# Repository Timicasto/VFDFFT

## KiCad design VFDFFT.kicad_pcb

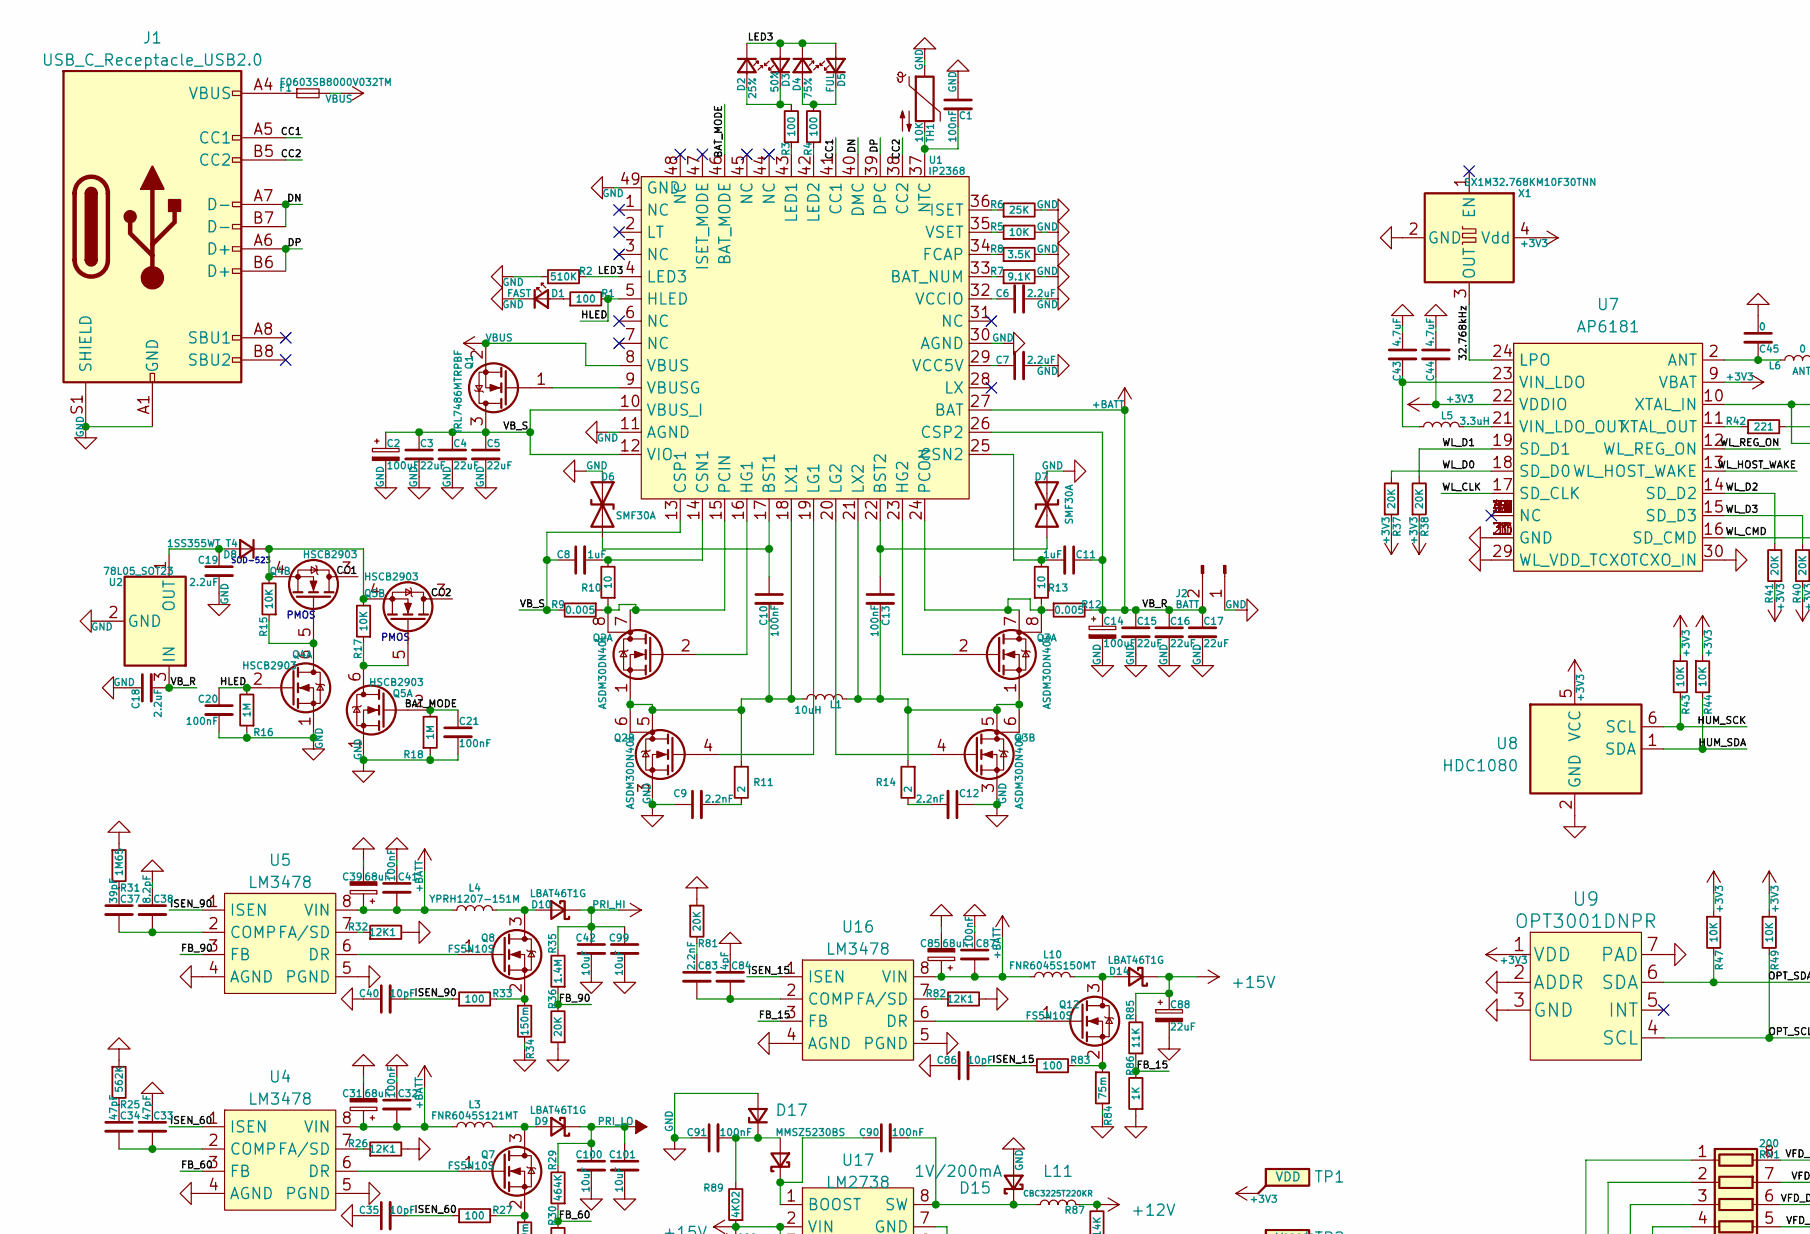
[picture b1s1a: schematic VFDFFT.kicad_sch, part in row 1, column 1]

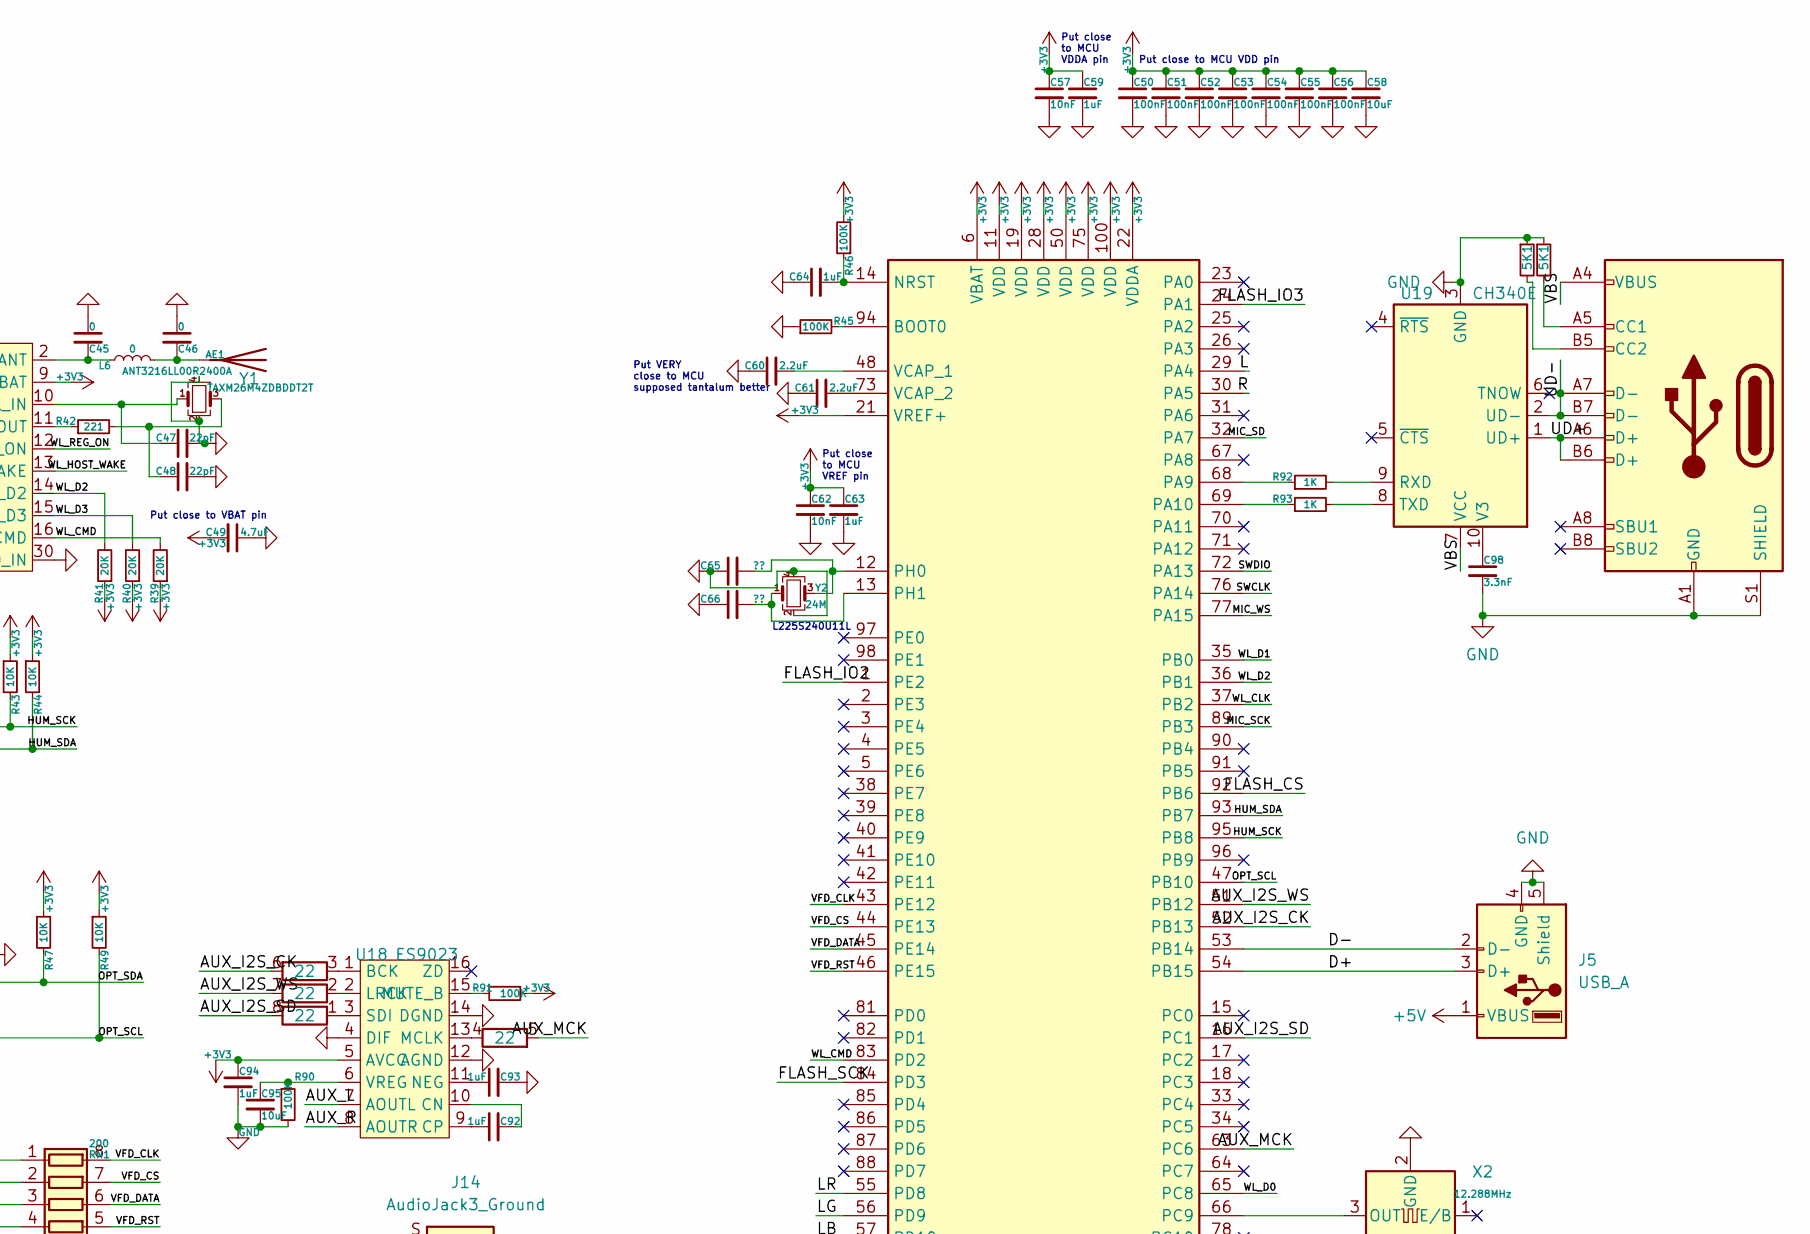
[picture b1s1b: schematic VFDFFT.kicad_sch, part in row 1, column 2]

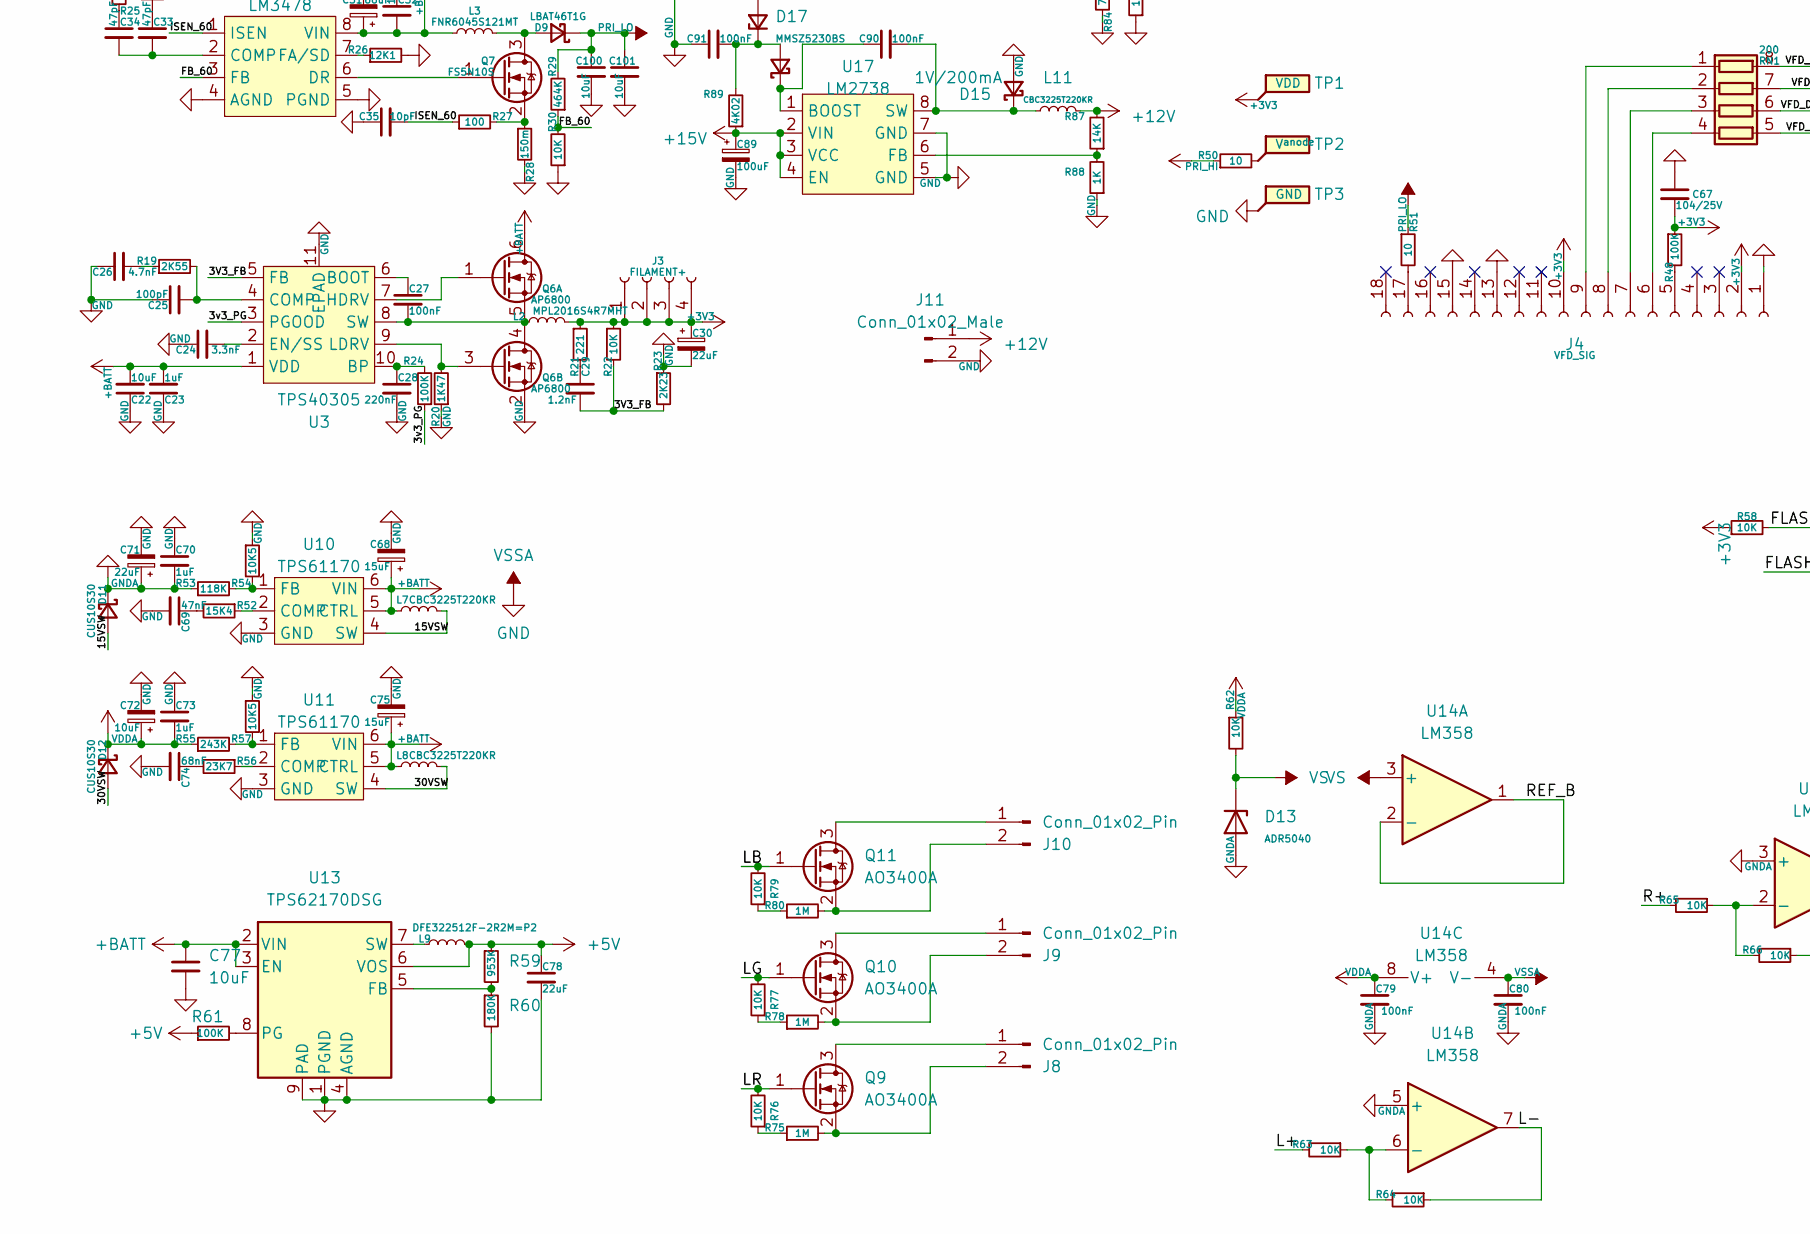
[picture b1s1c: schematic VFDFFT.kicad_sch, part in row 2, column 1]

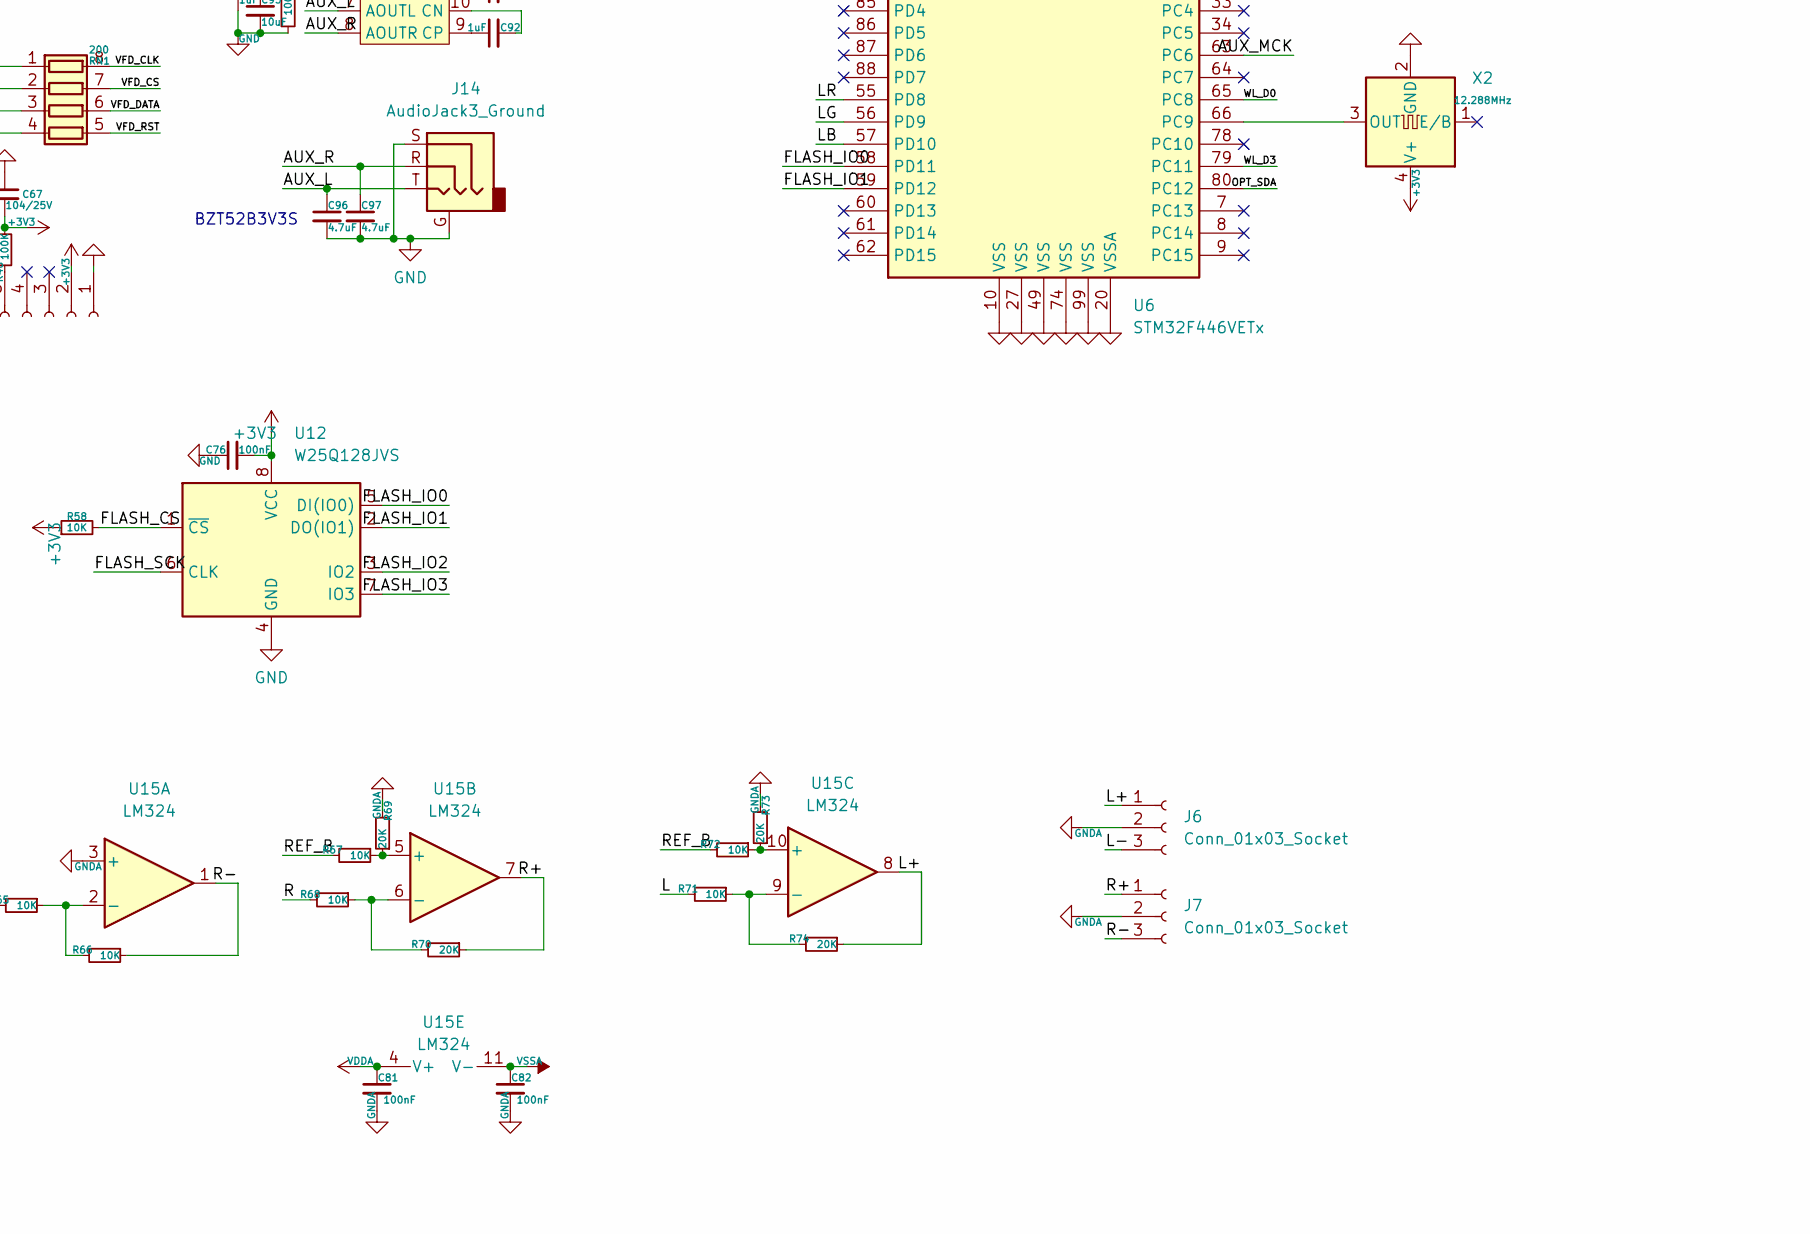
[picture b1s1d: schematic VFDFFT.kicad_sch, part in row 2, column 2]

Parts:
AE1: ANT3216LL00R2400A; R_1206_3216Metric
C1: 100nF; R_0603_1608Metric
C2, C14: 100uF; CP_EIA-7343-30_AVX-N
C3, C4, C5, C15, C16, C17, C71, C88: 22uF; C_0805_2012Metric
C6, C7, C18, C19, C60, C61: 2.2uF; C_0603_1608Metric
C8, C11, C23, C59, C63, C64, C70, C73, C92, C93, C94: 1uF; C_0603_1608Metric
C9, C12, C83: 2.2nF; C_0603_1608Metric
C10, C13, C20, C21, C27, C32, C41, C50, C51, C52, C53, C54, C55, C56, C76, C79, C80, C81, C82, C87, C90, C91: 100nF; C_0603_1608Metric
C22, C58, C72, C77, C95: 10uF; C_0603_1608Metric
C24, C98: 3.3nF; C_0603_1608Metric
C25: 100pF; C_0603_1608Metric
C26: 4.7nF; C_0603_1608Metric
C28: 220nF; C_0603_1608Metric
C29: 1.2nF; C_0603_1608Metric
C30, C78: 22uF; C_0603_1608Metric
C31, C39, C85: 68uF; CP_EIA-6032-28_Kemet-C
C33, C34: 47pF; C_0603_1608Metric
C35, C40, C86: 10pF; C_0603_1608Metric
C37: 39pF; C_0603_1608Metric
C38: 8.2pF; C_0603_1608Metric
C42, C99, C100, C101: 10uF; C_1210_3225Metric
C43, C44, C49, C96, C97: 4.7uF; C_0603_1608Metric
C45, C46: 0; C_0603_1608Metric
C47, C48: 22pF; C_0603_1608Metric
C57, C62: 10nF; C_0603_1608Metric
C65, C66: ??; C_0603_1608Metric
C67: 104/25V; C_0603_1608Metric
C68, C75: 15uF; C_0805_2012Metric
C69: 47nF; C_0603_1608Metric
C74: 68nF; C_0603_1608Metric
C84: 4pF; C_0603_1608Metric
C89: 100uF; C_0805_2012Metric
D1: FAST; D_0603_1608Metric
D2: 25%; D_0603_1608Metric
D3: 50%; D_0603_1608Metric
D4: 75%; D_0603_1608Metric
D5: FUL; D_0603_1608Metric
D6, D7: SMF30A; D_SOD-123F
D8: 1SS355WT T4; D_SOD-523
D9: LBAT46T1G; D_1206_3216Metric
D10: LBAT46T1G; SOD-323HE
D11, D12: CUS10S30; D_SOD-323
D13: ADR5040; SOT-23
D14: LBAT46T1G; D_SOD-123
D15, D16: 1V/200mA; D_SOD-523
D17: MMSZ5230BS; D_SOD-323
F1: F0603SB8000V032TM; Fuse_0603_1608Metric
J1, J15: USB_C_Receptacle_USB2.0; TYPE-C-31-M-31
J2: BATT; SolderWire-1sqmm_1x02_P5.4mm_D1.4mm_OD2.7mm
J3: FILAMENT+; PinHeader_1x04_P2.00mm_Vertical
J4: VFD_SIG; PinHeader_1x18_P2.00mm_Vertical
J5: USB_A; FCI_87520-0010BLF
J6, J7: Conn_01x03_Socket; PinSocket_1x03_P2.00mm_Vertical_SMD_Pin1Right
J8, J9, J10: Conn_01x02_Pin; PinSocket_1x02_P2.00mm_Vertical_SMD_Pin1Right
J11: Conn_01x02_Male; PinSocket_1x02_P2.00mm_Vertical_SMD_Pin1Right
J14: AudioJack3_Ground; TRRS-PJ-320A
L1: 10uH; L_11x10mm_H3.80
L2: MPL2016S4R7MHT; L_0806_2016Metric
L3: FNR6045S121MT; L_6.3x6.3_H3
L4: YPRH1207-151M; L_6.3x6.3_H3
L5: 3.3uH; L_1008_2520Metric
L6: 0; L_0603_1608Metric
L7, L8, L11: CBC3225T220KR; L_1210_3225Metric
L9: DFE322512F-2R2M=P2; L_1008_2520Metric
L10: FNR6045S150MT; L_6.3x6.3_H3
Q1: IRL7486MTRPBF; PDFN_3x3_GSD
Q2, Q3: ASDM30DN40E; PDFN3333-8
Q4, Q5: HSCB2903; DFN-6L-2EP-2x2
Q6: AP6800; SOT-23-6
Q7, Q8, Q12: FS5N10S; SOT-23
Q9, Q10, Q11: AO3400A; SOT-23
R1, R3, R4, R27, R33, R83: 100; R_0603_1608Metric
R2: 510K; R_0603_1608Metric
R5, R15, R17, R22, R30, R43, R44, R47, R49, R58, R62, R63, R64, R65, R66, R67, R68, R71, R72, R76, R77, R79: 10K; R_0603_1608Metric
R6: 25K; R_0603_1608Metric
R7: 9.1K; R_0603_1608Metric
R8: 3.5K; R_0603_1608Metric
R9: 0.005; R_1206_3216Metric
R10: 10; R_0805_2012Metric
R11, R14: 2; R_0603_1608Metric
R12: 0.005; R_0805_2012Metric
R13, R50, R51: 10; R_0603_1608Metric
R16, R18, R75, R78, R80: 1M; R_0603_1608Metric
R19: 2K55; R_0603_1608Metric
R20: 1K47; R_0603_1608Metric
R21, R42: 221; R_0603_1608Metric
R23: 2K23; R_0603_1608Metric
R24, R45, R46, R48, R61, R90, R91: 100K; R_0603_1608Metric
R25: 562K; R_0603_1608Metric
R26, R32, R82: 12K1; R_0603_1608Metric
R28, R34: 150m; R_0603_1608Metric
R29: 464K; R_0603_1608Metric
R31: 1M65; R_0603_1608Metric
R35: 1.4M; R_0603_1608Metric
R36, R37, R38, R39, R40, R41, R69, R70, R73, R74, R81: 20K; R_0603_1608Metric
R52: 15K4; R_0603_1608Metric
R53: 118K; R_0603_1608Metric
R54, R57: 10K5; R_0603_1608Metric
R55: 243K; R_0603_1608Metric
R56: 23K7; R_0603_1608Metric
R59: 953K; R_0603_1608Metric
R60: 180K; R_0603_1608Metric
R84: 75m; R_0603_1608Metric
R85: 11K; R_0603_1608Metric
R86, R88, R92, R93: 1K; R_0603_1608Metric
R87: 14K; R_0603_1608Metric
R89: 4K02; R_0603_1608Metric
R94, R95: 5K1; R_0603_1608Metric
RN1: 200; R_Array_Concave_4x0603
RN2: 22; R_Array_Concave_4x0603
TH1: 10K; R_0603_1608Metric
TP1: VDD; TestPoint_Pad_1.0x1.0mm
TP2: V^{anode}; TestPoint_Pad_1.0x1.0mm
TP3: GND; TestPoint_Pad_1.0x1.0mm
U1: IP2368; QFN-48-1EP_7x7mm_P0.5mm_EP5.3x5.3mm
U2: 78L05_SOT23; SOT-89-3
U3: TPS40305; DFN-10-1EP_3x3mm_P0.5mm_EP1.65x2.38mm
U4, U5, U16: LM3478; VSSOP-8_3.0x3.0mm_P0.65mm
U6: STM32F446VETx; LQFP-100_14x14mm_P0.5mm
U7: AP6181; QFN-44_12x12_Pitch0.9mm
U8: HDC1080; Texas_PWSON-N6
U9: OPT3001DNPR
U10, U11: TPS61170; WSON-6-1EP_2x2mm_P0.65mm_EP1x1.6mm
U12: W25Q128JVS; SOIC-8_5.23x5.23mm_P1.27mm
U13: TPS62170DSG; WSON-8-1EP_2x2mm_P0.5mm_EP0.9x1.6mm_ThermalVias
U14: LM358; VSSOP-8_3.0x3.0mm_P0.65mm
U15: LM324; TSSOP-14_4.4x5mm_P0.65mm
U17: LM2738; VSSOP-8_3.0x3.0mm_P0.65mm
U18: ES9023; SO-16_3.9x9.9mm_P1.27mm
U19: CH340E; MSOP-10_3x3mm_P0.5mm
X1: SX1M32.768KM10F30TNN; Crystal_SMD_2016-4Pin_2.0x1.6mm
X2: 12.288MHz; Crystal_SMD_2016-4Pin_2.0x1.6mm
Y1: TAXM26M4ZDBDDT2T; Crystal_SMD_2016-4Pin_2.0x1.6mm
Y2: 24M; Crystal_SMD_2016-4Pin_2.0x1.6mm

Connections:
+3V3: C30.1, C44.2, C49.2, C50.1, C51.1, C52.1, C53.1, C54.1, C55.1, C56.1, C57.1, C58.1, C59.1, C62.1, C63.1, C67.2, C76.2, C94.1, J3.1, J3.2, J3.3, J3.4, J4.2, J4.10, L2.2, R21.1, R22.1, R37.1, R38.1, R39.1, R40.1, R41.1, R43.1, R44.1, R46.2, R47.1, R48.1, R49.1, R58.1, R91.1, TP1.1, U6.6 (VBAT), U6.11 (VDD), U6.19 (VDD), U6.21 (VREF+), U6.22 (VDDA), U6.28 (VDD), U6.50 (VDD), U6.75 (VDD), U6.100 (VDD), U7.9 (VBAT), U7.22 (VDDIO), U8.5 (VCC), U9.1 (VDD), U12.8 (VCC), U18.5 (AVCC), X1.4 (Vdd), X2.4 (V+)
+5V: C78.1, J5.1 (VBUS), L9.2, R59.1, R61.1, U13.6 (VOS)
+12V: J11.1, L11.2, R87.2
+15V: C88.1, C89.1, D14.1 (K), R85.2, R89.1, U17.2 (VIN), U17.3 (VCC), U17.4 (EN)
+BATT: C11.1, C14.1, C15.1, C16.1, C17.1, C18.2, C22.2, C23.2, C31.1, C32.2, C39.1, C41.2, C68.1, C75.1, C77.1, C85.1, C87.2, J2.2, L3.1, L4.1, L7.1, L8.1, L10.1, Q6.6 (D), R12.2, U1.26 (CSP2), U1.27 (BAT), U2.3 (IN), U3.1 (VDD), U4.8 (VIN), U5.8 (VIN), U10.5 (CTRL), U10.6 (VIN), U11.5 (CTRL), U11.6 (VIN), U13.2 (VIN), U13.3 (EN), U16.8 (VIN)
/3V3_FB: C29.2, R22.2, R23.2, U3.5 (FB)
/3v3_PG: R24.1, U3.3 (PGOOD)
/15VSW: D11.2 (A), L7.2, U10.4 (SW)
/30VSW: D12.2 (A), L8.2, U11.4 (SW)
/32.768kHz: U7.24 (LPO), X1.3 (OUT)
/AUX_I2S_CK: RN2.6 (R3.2), U6.52 (PB13)
/AUX_I2S_SD: RN2.8 (R1.2), U6.16 (PC1)
/AUX_I2S_WS: RN2.7 (R2.2), U6.51 (PB12)
/AUX_L: C96.1, J14.T, U18.7 (AOUTL)
/AUX_MCK: RN2.5 (R4.2), U6.63 (PC6)
/AUX_R: C97.1, J14.R, U18.8 (AOUTR)
/BAT_MODE: C21.1, Q5.2 (G), R18.2, U1.46 (BAT_MODE)
/CC1: J1.A5 (CC1), Q4.3 (D), U1.41 (CC1)
/CC2: J1.B5 (CC2), Q5.3 (D), U1.38 (CC2)
/D+: J5.3 (D+), U6.54 (PB15)
/D-: J5.2 (D-), U6.53 (PB14)
/DN: J1.A7 (D-), J1.B7 (D-), U1.40 (DMC)
/DP: J1.A6 (D+), J1.B6 (D+), U1.39 (DPC)
/FB_15: R85.1, R86.2, U16.3 (FB)
/FB_60: R29.1, R30.2, U4.3 (FB)
/FB_90: R35.1, R36.2, U5.3 (FB)
/FLASH_CS: R58.2, U6.92 (PB6), U12.1 (~CS)
/FLASH_IO0: U6.58 (PD11), U12.5 (DI(IO0))
/FLASH_IO1: U6.59 (PD12), U12.2 (DO(IO1))
/FLASH_IO2: U6.1 (PE2), U12.3 (IO2)
/FLASH_IO3: U6.24 (PA1), U12.7 (IO3)
/FLASH_SCK: U6.84 (PD3), U12.6 (CLK)
/HLED: C20.1, Q4.2 (G), R1.2, R16.2, U1.5 (HLED)
/HUM_SCK: R43.2, U6.95 (PB8), U8.6 (SCL)
/HUM_SDA: R44.2, U6.93 (PB7), U8.1 (SDA)
/ISEN_15: C86.2, R83.1, U16.1 (ISEN)
/ISEN_60: C35.2, R27.1, U4.1 (ISEN)
/ISEN_90: C40.2, R33.1, U5.1 (ISEN)
/L: R71.2, U6.29 (PA4)
/L+: J6.1, R63.2, R74.1, U15.8
/L-: J6.3, R64.1, U14.7
/LB: Q11.1 (G), R79.2, U6.57 (PD10)
/LED3: D2.1 (K), D3.2 (A), D4.1 (K), D5.2 (A), R2.2, U1.4 (LED3)
/LG: Q10.1 (G), R77.2, U6.56 (PD9)
/LR: Q9.1 (G), R76.2, U6.55 (PD8)
/MIC_SCK: U6.89 (PB3)
/MIC_SD: U6.32 (PA7)
/MIC_WS: U6.77 (PA15)
/OPT_SCL: R49.2, U6.47 (PB10), U9.4 (SCL)
/OPT_SDA: R47.2, U6.80 (PC12), U9.6 (SDA)
/R: R68.2, U6.30 (PA5)
/R+: J7.1, R65.2, R70.1, U15.7
/R-: J7.3, R66.1, U15.1
/REF_B: R67.2, R72.2, U14.1, U14.2 (-)
/SWCLK: U6.76 (PA14)
/SWDIO: U6.72 (PA13)
/UD+: J15.A6 (D+), J15.B6 (D+), U19.1 (UD+)
/UD-: J15.A7 (D-), J15.B7 (D-), U19.2 (UD-)
/VBS: J15.A4 (VBUS), J15.A9 (VBUS), J15.B4 (VBUS), J15.B9 (VBUS), U19.7 (VCC)
/VB_S: C2.1, C3.1, C4.1, C5.1, C8.1, Q1.3 (D), R9.2, U1.10 (VBUS_I), U1.12 (VIO), U1.13 (CSP1)
/VFD_CLK: RN1.8 (R1.2), U6.43 (PE12)
/VFD_CS: RN1.7 (R2.2), U6.44 (PE13)
/VFD_DATA: RN1.6 (R3.2), U6.45 (PE14)
/VFD_RST: RN1.5 (R4.2), U6.46 (PE15)
/WL_CLK: U6.37 (PB2), U7.17 (SD_CLK)
/WL_CMD: R39.2, U6.83 (PD2), U7.16 (SD_CMD)
/WL_D0: R37.2, U6.65 (PC8), U7.18 (SD_D0)
/WL_D1: R38.2, U6.35 (PB0), U7.19 (SD_D1)
/WL_D2: R41.2, U6.36 (PB1), U7.14 (SD_D2)
/WL_D3: R40.2, U6.79 (PC11), U7.15 (SD_D3)
/WL_HOST_WAKE: U7.13 (WL_HOST_WAKE)
/WL_REG_ON: U7.12 (WL_REG_ON)
GND: C1.1, C2.2, C3.2, C4.2, C5.2, C6.2, C7.2, C9.1, C12.1, C14.2, C15.2, C16.2, C17.2, C18.1, C19.2, C20.2, C21.2, C22.1, C23.1, C24.1, C25.1, C26.1, C28.2, C30.2, C31.2, C32.1, C33.1, C35.1, C38.1, C39.2, C40.1, C41.1, C42.2, C43.1, C44.1, C45.1, C46.1, C47.2, C48.2, C49.1, C50.2, C51.2, C52.2, C53.2, C54.2, C55.2, C56.2, C57.2, C58.2, C59.2, C60.1, C61.1, C62.2, C63.2, C64.1, C65.1, C66.1, C67.1, C68.2, C69.2, C70.1, C71.2, C72.2, C73.1, C74.2, C75.2, C76.1, C77.2, C78.2, C80.1, C82.1, C84.1, C85.2, C86.1, C87.1, C88.2, C89.2, C91.1, C93.2, C94.2, C95.2, C96.2, C97.2, C98.2, C99.2, C100.2, C101.2, D1.1 (K), D6.1 (A1), D7.1 (A1), D15.2 (A), D17.2 (A), J1.A1 (GND), J1.A12 (GND), J1.B1 (GND), J1.B12 (GND), J1.S1 (SHIELD), J2.1, J4.1, J4.13, J4.15, J5.4 (GND), J5.5 (Shield), J11.2, J14.G, J14.S, J15.A1 (GND), J15.A12 (GND), J15.B1 (GND), J15.B12 (GND), J15.S1 (SHIELD), Q2.3 (S), Q3.3 (S), Q4.1 (S), Q5.1 (S), Q6.2 (S), R2.1, R5.2, R6.2, R7.2, R8.2, R16.1, R18.1, R20.1, R23.1, R25.1, R26.2, R28.2, R30.1, R31.1, R32.2, R34.2, R36.1, R45.1, R54.1, R57.1, R60.2, R81.1, R82.2, R84.2, R86.1, R88.1, R90.2, R94.1, R95.1, TH1.1, TP3.1, U1.11 (AGND), U1.30 (AGND), U1.49 (GND), U2.2 (GND), U3.11 (EPAD), U4.4 (AGND), U4.5 (PGND), U5.4 (AGND), U5.5 (PGND), U6.10 (VSS), U6.20 (VSSA), U6.27 (VSS), U6.49 (VSS), U6.74 (VSS), U6.99 (VSS), U7.1 (GND), U7.3 (GND), U7.20 (GND), U7.29 (WL_VDD_TCXO), U7.30 (TCXO_IN), U7.31 (GND), U7.33 (GND), U8.2 (GND), U9.2 (ADDR), U9.3 (GND), U9.7 (PAD), U10.3 (GND), U11.3 (GND), U12.4 (GND), U13.1 (PGND), U13.4 (AGND), U13.9 (PAD), U14.4 (V-), U15.11 (V-), U16.4 (AGND), U16.5 (PGND), U17.5 (GND), U17.7 (GND), U17.9 (GND), U18.4 (DIF), U18.12 (AGND), U18.14 (DGND), U19.3 (GND), X1.2 (GND), X2.2 (GND), Y1.2, Y1.4, Y2.2, Y2.4
GNDA: C70.2, C71.1, C79.2, C80.2, C81.2, C82.2, D11.1 (K), D13.2 (A), J6.2, J7.2, R53.1, R69.2, R73.2, U14.5 (+), U15.3 (+)
unnamed: AE1.1 (A), C46.2, L6.2
unnamed: C9.2, R11.2
unnamed: C12.2, R14.2
unnamed: C26.2, R19.1
unnamed: C29.1, R21.2
unnamed: C34.1, R25.2
unnamed: C37.1, R31.2
unnamed: C48.1, R42.2, Y1.3
unnamed: C69.1, R52.2
unnamed: C74.1, R56.2
unnamed: C83.1, R81.2
unnamed: D1.2 (A), R1.1
unnamed: D2.2 (A), D3.1 (K), R3.2
unnamed: D4.2 (A), D5.1 (K), R4.2
unnamed: C10.1, D6.2 (A2), U1.17 (BST1)
unnamed: C13.1, D7.2 (A2), U1.22 (BST2)
unnamed: C19.1, D8.2 (A), U2.1 (OUT)
unnamed: D8.1 (K), Q4.4 (S), Q5.4 (S), R15.2, R17.2
unnamed: D9.2 (A), L3.2, Q7.3 (D)
unnamed: D10.2 (A), L4.2, Q8.3 (D)
unnamed: D14.2 (A), L10.2, Q12.3 (D)
unnamed: C90.2, D15.1 (K), L11.1, U17.8 (SW)
unnamed: C91.2, D16.2 (A), D17.1 (K), R89.2
unnamed: C90.1, D16.1 (K), U17.1 (BOOST)
unnamed: F1.1, J1.A4 (VBUS), J1.A9 (VBUS), J1.B4 (VBUS), J1.B9 (VBUS)
unnamed: J4.5, R48.2
unnamed: J4.6, RN1.4 (R4.1)
unnamed: J4.7, RN1.3 (R3.1)
unnamed: J4.8, RN1.2 (R2.1)
unnamed: J4.9, RN1.1 (R1.1)
unnamed: J4.17, R51.2
unnamed: J8.1, Q9.3 (D)
unnamed: J8.2, Q9.2 (S), R75.2
unnamed: J9.1, Q10.3 (D)
unnamed: J9.2, Q10.2 (S), R78.2
unnamed: J10.1, Q11.3 (D)
unnamed: J10.2, Q11.2 (S), R80.2
unnamed: J15.A5 (CC1), R95.2
unnamed: J15.B5 (CC2), R94.2
unnamed: Q1.1 (G), U1.9 (VBUSG)
unnamed: Q2.2 (G), U1.16 (HG1)
unnamed: C10.2, L1.1, Q2.1 (S), Q2.5 (D), Q2.6 (D), R11.1, U1.18 (LX1)
unnamed: Q2.4 (G), U1.19 (LG1)
unnamed: Q3.2 (G), U1.23 (HG2)
unnamed: C13.2, L1.2, Q3.1 (S), Q3.5 (D), Q3.6 (D), R14.1, U1.21 (LX2)
unnamed: Q3.4 (G), U1.20 (LG2)
unnamed: Q4.5 (G), Q4.6 (D), R15.1
unnamed: Q5.5 (G), Q5.6 (D), R17.1
unnamed: Q6.1 (G), U3.7 (HDRV)
unnamed: C27.2, L2.1, Q6.4 (D), Q6.5 (S), U3.8 (SW)
unnamed: Q6.3 (G), R20.2, U3.9 (LDRV)
unnamed: Q7.1 (G), U4.6 (DR)
unnamed: Q7.2 (S), R27.2, R28.1
unnamed: Q8.1 (G), U5.6 (DR)
unnamed: Q8.2 (S), R33.2, R34.1
unnamed: Q12.1 (G), U16.6 (DR)
unnamed: Q12.2 (S), R83.2, R84.1
unnamed: R50.2, TP2.1
unnamed: R75.1, R76.1
unnamed: R77.1, R78.1
unnamed: R79.1, R80.1
unnamed: RN2.1 (R1.1), U18.3 (SDI)
unnamed: RN2.2 (R2.1), U18.2 (LRCK)
unnamed: RN2.3 (R3.1), U18.1 (BCK)
unnamed: RN2.4 (R4.1), U18.13 (MCLK)
unnamed: R7.1, U1.33 (BAT_NUM)
unnamed: C8.2, R10.2, U1.14 (CSN1)
unnamed: C11.2, R13.2, U1.25 (CSN2)
unnamed: R8.1, U1.34 (FCAP)
unnamed: R6.1, U1.36 (ISET)
unnamed: R3.1, U1.43 (LED1)
unnamed: R4.1, U1.42 (LED2)
unnamed: C1.2, TH1.2, U1.37 (NTC)
unnamed: Q2.7 (D), Q2.8 (D), R9.1, R10.1, U1.15 (PCIN)
unnamed: Q3.7 (D), Q3.8 (D), R12.1, R13.1, U1.24 (PCON)
unnamed: C7.1, U1.29 (VCC5V)
unnamed: C6.1, U1.32 (VCCIO)
unnamed: R5.1, U1.35 (VSET)
unnamed: C27.1, U3.6 (BOOT)
unnamed: C28.1, R24.2, U3.10 (BP)
unnamed: C25.2, R19.2, U3.4 (COMP)
unnamed: C24.2, U3.2 (EN/SS)
unnamed: C33.2, C34.2, U4.2 (COMP)
unnamed: R26.1, U4.7 (FA/SD)
unnamed: C37.2, C38.2, U5.2 (COMP)
unnamed: R32.1, U5.7 (FA/SD)
unnamed: R45.2, U6.94 (BOOT0)
unnamed: C64.2, R46.1, U6.14 (NRST)
unnamed: R92.1, U6.68 (PA9)
unnamed: R93.1, U6.69 (PA10)
unnamed: U6.66 (PC9), X2.3 (OUT)
unnamed: C65.2, U6.12 (PH0), Y2.3
unnamed: C66.2, U6.13 (PH1), Y2.1
unnamed: C60.2, U6.48 (VCAP_1)
unnamed: C61.2, U6.73 (VCAP_2)
unnamed: C45.2, L6.1, U7.2 (ANT)
unnamed: C43.2, L5.1, U7.23 (VIN_LDO)
unnamed: L5.2, U7.21 (VIN_LDO_OUT)
unnamed: C47.1, U7.10 (XTAL_IN), Y1.1
unnamed: R42.1, U7.11 (XTAL_OUT)
unnamed: R52.1, U10.2 (COMP)
unnamed: R53.2, R54.2, U10.1 (FB)
unnamed: R56.1, U11.2 (COMP)
unnamed: R55.2, R57.2, U11.1 (FB)
unnamed: R59.2, R60.1, U13.5 (FB)
unnamed: R61.2, U13.8 (PG)
unnamed: L9.1, U13.7 (SW)
unnamed: R63.1, R64.2, U14.6 (-)
unnamed: R65.1, R66.2, U15.2 (-)
unnamed: R67.1, R69.1, U15.5 (+)
unnamed: R68.1, R70.2, U15.6 (-)
unnamed: R72.1, R73.1, U15.10 (+)
unnamed: R71.1, R74.2, U15.9 (-)
unnamed: C83.2, C84.2, U16.2 (COMP)
unnamed: R82.1, U16.7 (FA/SD)
unnamed: R87.1, R88.2, U17.6 (FB)
unnamed: C92.2, U18.10 (CN)
unnamed: C92.1, U18.9 (CP)
unnamed: R91.2, U18.15 (MUTE_B)
unnamed: C93.1, U18.11 (NEG)
unnamed: C95.1, R90.1, U18.6 (VREG)
unnamed: R92.2, U19.9 (RXD)
unnamed: R93.2, U19.8 (TXD)
unnamed: C98.1, U19.10 (V3)
PRI_HI: C42.1, C99.1, D10.1 (K), R35.2, R50.1
PRI_LO: C100.1, C101.1, D9.1 (K), R29.2, R51.1
VBUS: F1.2, Q1.2 (S), U1.8 (VBUS)
VDDA: C72.1, C73.2, C79.1, C81.1, D12.1 (K), R55.1, R62.1, U14.8 (V+), U15.4 (V+)
VS: D13.1 (K), R62.2, U14.3 (+)

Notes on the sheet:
Put close to MCU VDDA pin
Put VERY close to MCU supposed tantalum better
Put close to MCU VREF pin
SOD-523
Put close to MCU VDD pin
BZT52B3V3S
PMOS
L225S240U11L
Put close to VBAT pin

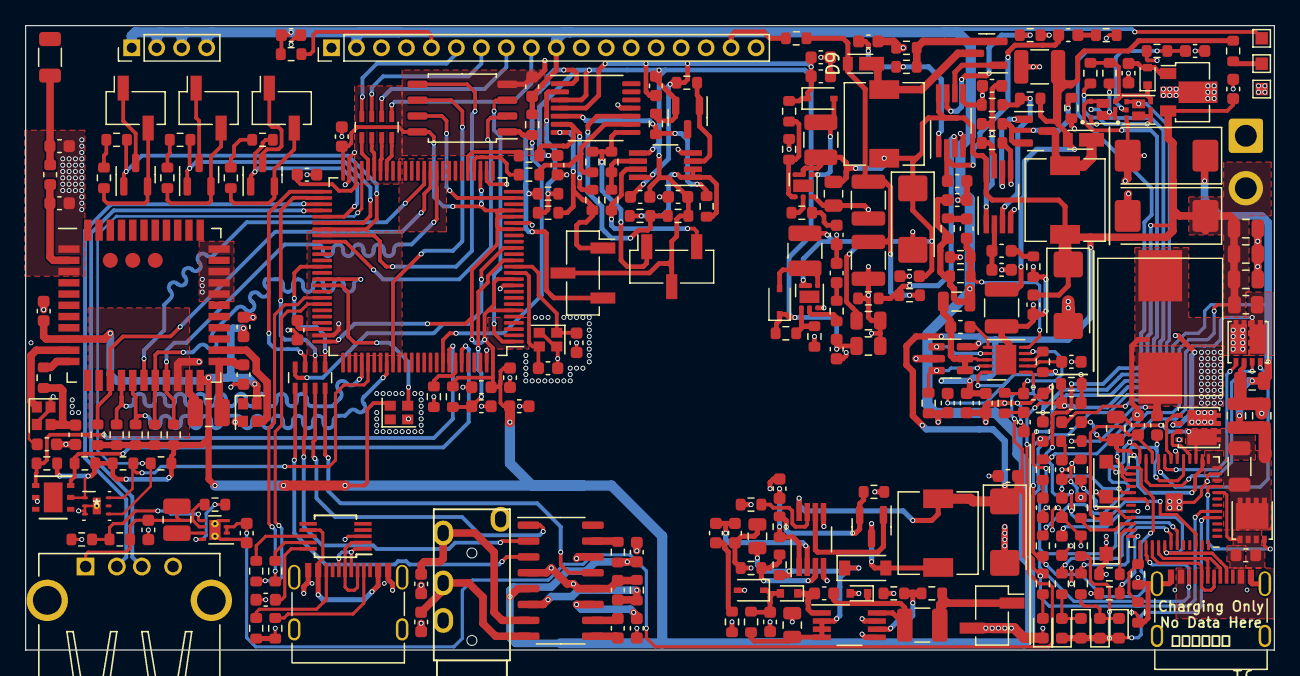
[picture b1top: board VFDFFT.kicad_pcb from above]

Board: 2 copper layers, 100.0 x 50.0 mm, 271 parts (0 on the bottom side), 196 nets.

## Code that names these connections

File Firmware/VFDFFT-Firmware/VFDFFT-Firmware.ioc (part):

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Mcu.Name=STM32F446V(C-E)Tx
Mcu.Package=LQFP100
Mcu.UserName=STM32F446VETx
PA0-WKUP.Mode=Half_duplex(single_wire_mode)
PA0-WKUP.Signal=UART4_TX
PA10.Mode=Asynchronous
PA10.Signal=USART1_RX
PA13.Mode=Serial_Wire
PA13.Signal=SYS_JTMS-SWDIO
PA14.Mode=Serial_Wire
PA14.Signal=SYS_JTCK-SWCLK
PA15.Mode=Half_Duplex_Slave
PA15.Signal=I2S1_WS
PA4.Signal=COMP_DAC1_group
PA5.Signal=COMP_DAC2_group
PA6.Mode=Master_Clock_Activated
PA6.Signal=I2S2_MCK
PA7.Mode=Half_Duplex_Slave
PA7.Signal=I2S1_SD
PA9.Mode=Asynchronous
PA9.Signal=USART1_TX
PB0.Mode=SD_4_bits_Wide_bus
PB0.Signal=SDIO_D1
PB1.Mode=SD_4_bits_Wide_bus
PB1.Signal=SDIO_D2
PB10.Mode=I2C
PB10.Signal=I2C2_SCL
PB12.Mode=Half_Duplex_Master
PB12.Signal=I2S2_WS
PB13.Mode=Half_Duplex_Master
PB13.Signal=I2S2_CK
PB14.Mode=Host_FS
PB14.Signal=USB_OTG_HS_DM
PB15.Mode=Host_FS
PB15.Signal=USB_OTG_HS_DP
PB2.Mode=SD_4_bits_Wide_bus
PB2.Signal=SDIO_CK
PB3.Mode=Half_Duplex_Slave
PB3.Signal=I2S1_CK
PB6.Mode=Single Bank 1
PB6.Signal=QUADSPI_BK1_NCS
PB7.Mode=I2C
PB7.Signal=I2C1_SDA
PB8.Mode=I2C
PB8.Signal=I2C1_SCL
PC0.Signal=GPIO_Output
PC1.Mode=Half_Duplex_Master
PC1.Signal=I2S2_SD
PC11.Mode=SD_4_bits_Wide_bus
PC11.Signal=SDIO_D3
PC12.Mode=I2C
PC12.Signal=I2C2_SDA
PC8.Mode=SD_4_bits_Wide_bus
PC8.Signal=SDIO_D0
PC9.Mode=Audio_ClockIn
PC9.Signal=I2S_CKIN
PD11.Mode=Single Bank 1
PD11.Signal=QUADSPI_BK1_IO0
PD12.Mode=Single Bank 1
PD12.Signal=QUADSPI_BK1_IO1
PD13.Mode=Single Bank 1
PD13.Signal=QUADSPI_BK1_IO3
PD2.Mode=SD_4_bits_Wide_bus
PD2.Signal=SDIO_CMD
PD3.Mode=Single Bank 1
PD3.Signal=QUADSPI_CLK
PE12.Mode=TX_Only_Simplex_Unidirect_Master
PE12.Signal=SPI4_SCK
PE13.Signal=GPIO_Output
PE14.Mode=TX_Only_Simplex_Unidirect_Master
PE14.Signal=SPI4_MOSI
PE15.Signal=GPIO_Output
PE2.Mode=Single Bank 1
PE2.Signal=QUADSPI_BK1_IO2
PE4.Signal=GPIO_Output
PE5.Signal=GPIO_Output
PE6.Signal=GPIO_Output
PH0-OSC_IN.Mode=HSE-External-Oscillator
PH0-OSC_IN.Signal=RCC_OSC_IN
PH1-OSC_OUT.Mode=HSE-External-Oscillator
PH1-OSC_OUT.Signal=RCC_OSC_OUT
RCC.HSE_VALUE=24000000
RCC.SYSCLKFreq_VALUE=180000000
RCC.SYSCLKSource=RCC_SYSCLKSOURCE_PLLCLK
board=custom

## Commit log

2023-01-05 assign footprint 30%
2023-01-08 complete almost schem
2023-01-09 file sync
2023-01-09 schem complete
2023-01-11 SDIO routing
2023-01-13 Laser ON/OFF
2023-01-17 Sensor Code
2023-01-18 Lasesr GPIO
2023-01-19 NOR FLASH
